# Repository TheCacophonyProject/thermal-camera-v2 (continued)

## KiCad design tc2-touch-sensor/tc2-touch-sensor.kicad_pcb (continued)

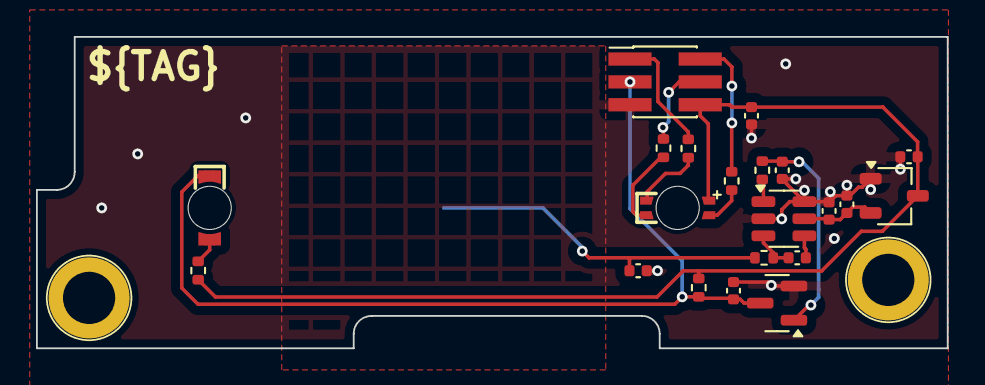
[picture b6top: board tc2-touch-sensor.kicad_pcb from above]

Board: 6 copper layers, 50.6 x 17.3 mm, 24 parts (1 on the bottom side), 16 nets.

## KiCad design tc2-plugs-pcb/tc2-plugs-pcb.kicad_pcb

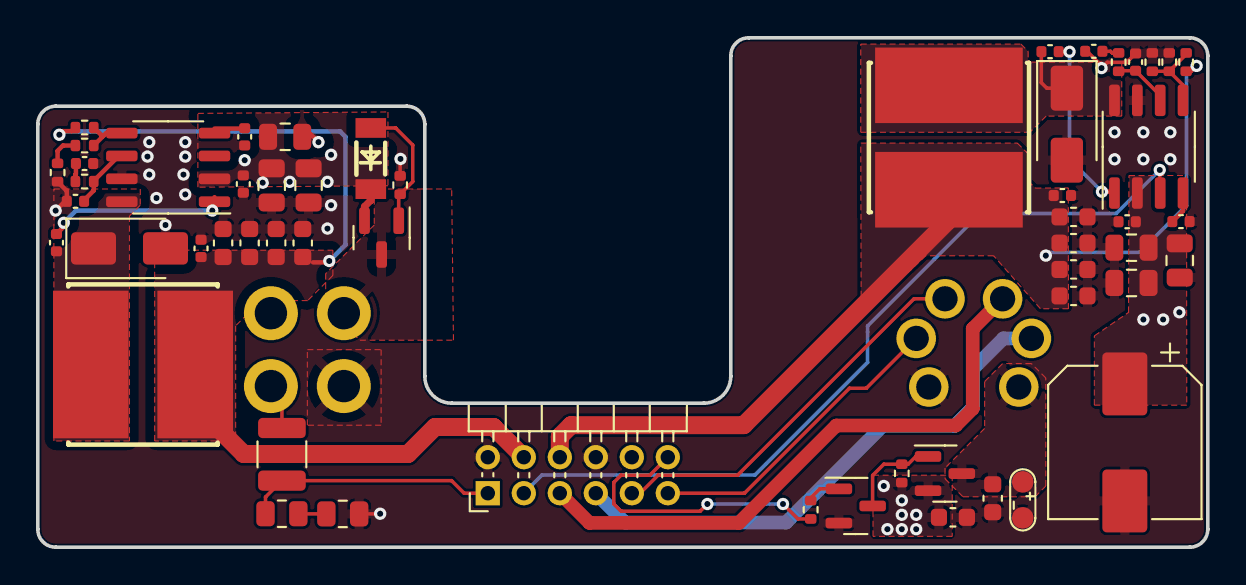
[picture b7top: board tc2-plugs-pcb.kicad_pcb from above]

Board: 4 copper layers, 65.0 x 28.3 mm, 57 parts (0 on the bottom side), 31 nets.

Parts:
C101, C102, C103, C104, C106, C107: 22uF; C_0805_2012Metric
C105: 220uF; CP_Elec_8x10
C108, C129: 10uF; C_0603_1608Metric
C109, C110, C111, C112, C119, C120: 1nF; C_0402_1005Metric
C113, C114: 47pF; C_0402_1005Metric
C115, C116: 10nF; C_0402_1005Metric
C117, C118: 100nF; C_0402_1005Metric
C121, C122, C123, C124, C125, C126, C127, C128: 22uF; C_0603_1608Metric
D101: D_Zener; LL-34_L3.5-W1.5-RD
D102, D103: D_Shockley; D_SMA
J102: JCON_M16_04Pin; jcon-4pin_m16
J103: JCON_M16_06Pin; jcon-6pin-m16
J104: Conn_02x06_Odd_Even; PinHeader_2x06_P2.00mm_Horizontal
L101, L102: 6.8uF; IND-SMD_L8.0-W8.0_1217AS
Q101, Q102: Q_PMOS_GSD; SOT-23
Q103: 2N7002; SOT-23
R101: 2M; R_1210_3225Metric
R102: 150k; R_0805_2012Metric
R103: 22k; R_0805_2012Metric
R104, R110, R112, R113: 100k; R_0402_1005Metric
R105, R106: 33k; R_0402_1005Metric
R107: 150k; R_0402_1005Metric
R108, R111: 22k; R_0402_1005Metric
R109: 10k; R_0402_1005Metric
R114: 1k; R_0402_1005Metric
TP101: TestPoint_2Pole; test-point-2p
U101, U102: TPS54331; SO-8_3.9x4.9mm_P1.27mm

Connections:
5V_EN: J104.3, U101.3 (EN)
+3V3: C120.1, C122.1, C124.1, C126.1, C128.1, J104.4, L102.2, R112.1
+5V: C119.1, C121.1, C123.1, C125.1, C127.1, J104.6, L101.2, R110.1
+12V: C101.1, C102.1, C103.1, C104.1, C105.1, C106.1, C107.1, C109.1, C110.1, C129.1, D101.1 (K), Q101.2 (S), Q102.2 (S), R113.2, U101.2 (VIN), U102.2 (VIN)
/+Batt: J102.4, R101.1
/SW_3V3: C118.2, D103.1 (K), L102.1, U102.8 (PH)
/SW_5V: C117.2, D102.1 (K), L101.1, U101.8 (PH)
BATT_SENSE: J104.1, R101.2, R102.1
EN_PERIPH: J104.12, R114.1
GND: C101.2, C102.2, C103.2, C104.2, C105.2, C106.2, C107.2, C108.2, C109.2, C110.2, C111.2, C112.2, C113.2, C114.2, C115.2, C116.2, C119.2, C120.2, C121.2, C122.2, C123.2, C124.2, C125.2, C126.2, C127.2, C128.2, C129.2, D102.2 (A), D103.2 (A), J102.1, J103.1, J104.2, J104.8, Q103.2 (S), R103.2, R104.2, R107.1, R109.2, R111.1, TP101.1, U101.7 (GND), U102.7 (GND)
unnamed: C111.1, R105.2
unnamed: C112.1, R106.2
unnamed: D101.2 (A), Q101.1 (G), R104.1
unnamed: Q102.1 (G), Q103.3 (D), R113.1
unnamed: Q103.1 (G), R114.2
unnamed: R102.2, R103.1
unnamed: R108.1, R109.1
unnamed: C117.1, U101.1 (BOOT)
unnamed: C113.1, R105.1, U101.6 (COMP)
unnamed: C115.1, U101.4 (SS)
unnamed: R107.2, R110.2, R111.2, U101.5 (VSENSE)
unnamed: C118.1, U102.1 (BOOT)
unnamed: C114.1, R106.1, U102.6 (COMP)
unnamed: C116.1, U102.4 (SS)
unnamed: R108.2, R112.2, U102.5 (VSENSE)
OUT_RX: J103.2, J104.11
OUT_TX: J103.3, J104.9
SPEAKER_+: J103.4, J104.5
SPEAKER_-: J103.5, J104.7
VIN: J102.2, Q101.3 (D)
VOUT: C108.1, J103.6, Q102.3 (D), TP101.2

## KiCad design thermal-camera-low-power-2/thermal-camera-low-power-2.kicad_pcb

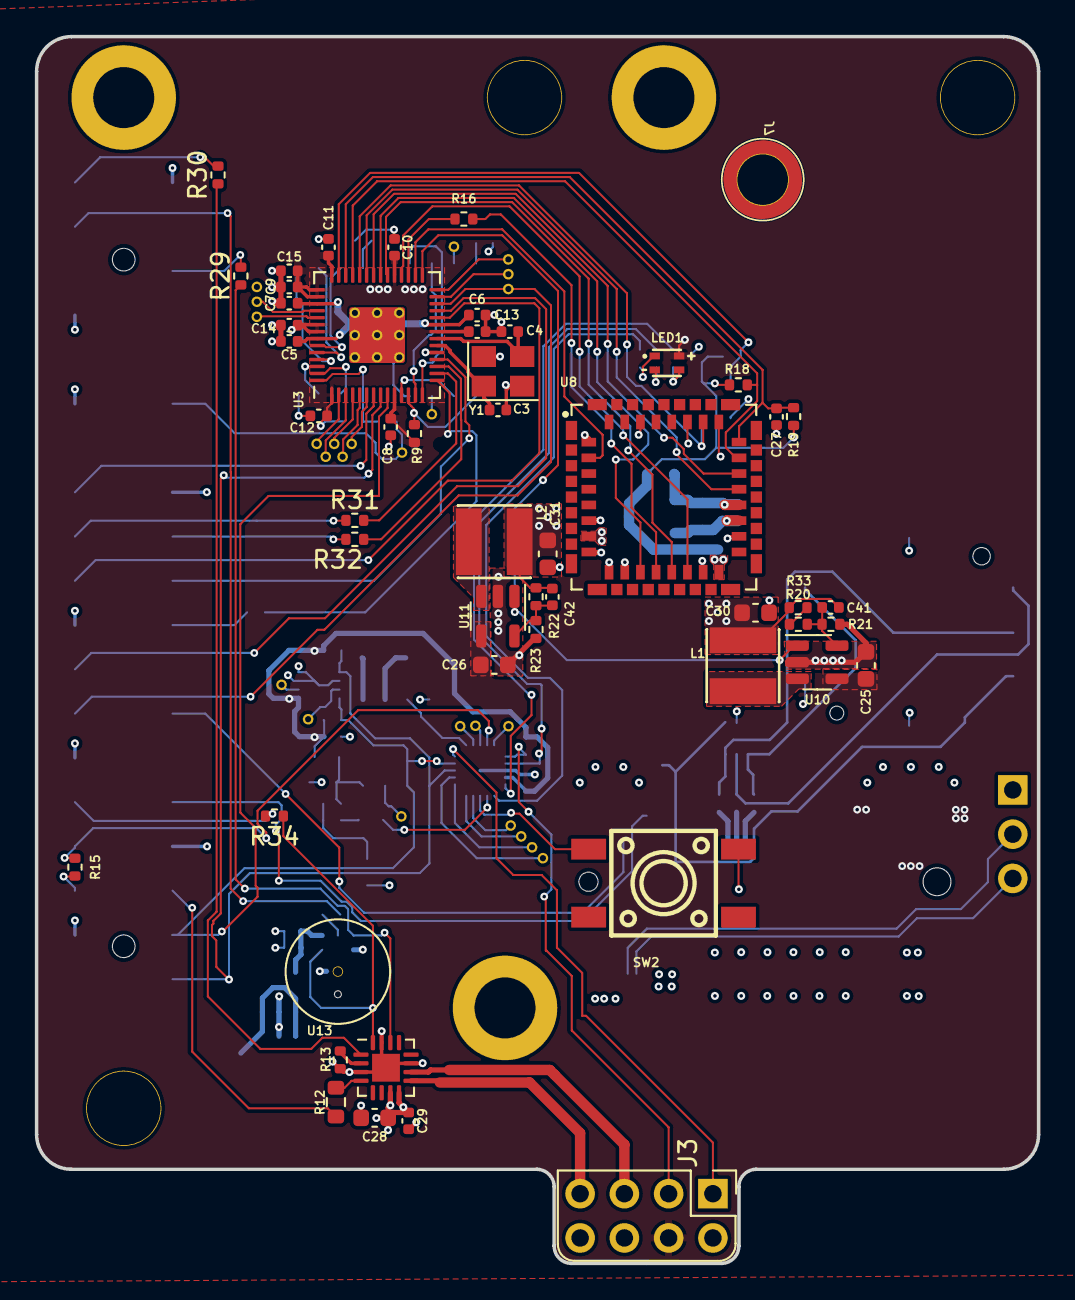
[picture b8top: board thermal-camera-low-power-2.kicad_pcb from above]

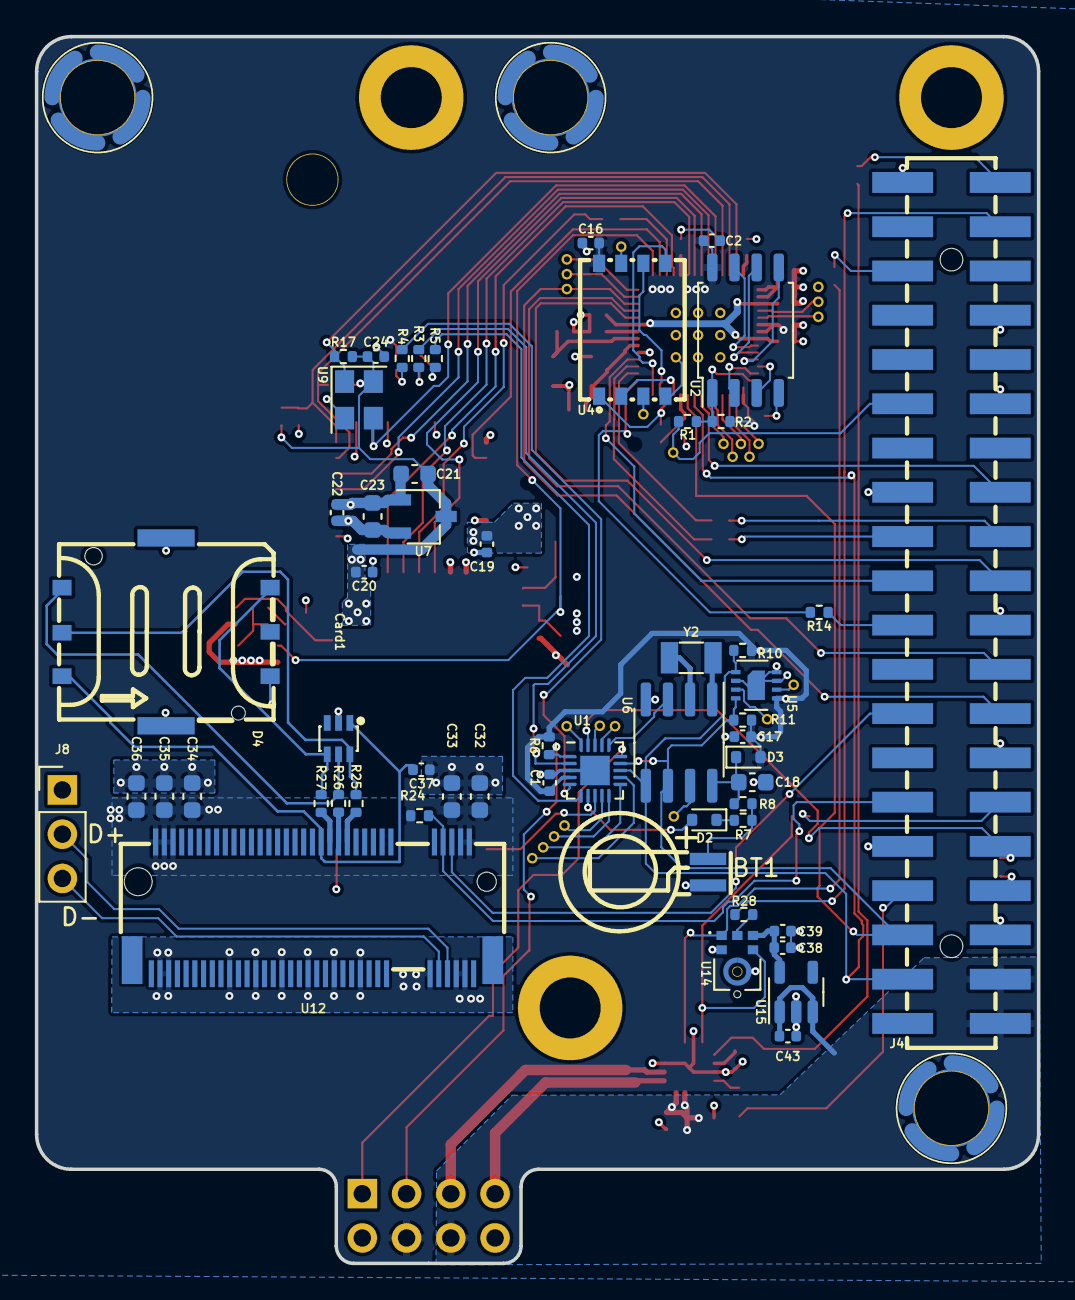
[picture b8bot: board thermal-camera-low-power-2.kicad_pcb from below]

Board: 4 copper layers, 57.5 x 70.4 mm, 136 parts (69 on the bottom side), 115 nets.

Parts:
BT1: Battery_Cell; CAP-SMD_FL11E
C1, C2, C5, C6, C8, C10, C11, C12, C13, C14, C15, C16, C17, C19, C20, C22, C24, C27, C29, C37, C38: 220nF; C_0402_1005Metric
C3, C4, C39, C41, C42: 12pF; C_0402_1005Metric
C7, C9: 1u; C_0402_1005Metric
C18, C21, C23, C25, C26, C28, C30, C31, C32, C33, C34, C35, C36: 10uF; C_0603_1608Metric
C43: 1uF; C_0402_1005Metric
Card1: SIM-Nano; SIM-SMD_SMN-304
D2, D3: D; D_SOD-523
D4: SMF05CT1G; SOT-363_L2.0-W1.3-P0.65-LS2.1-BR
H1, H2, H3: MountingHole; Mouning_Hole_M3
J1, J5, J6: Screw_Terminal_01x01; SMTSO25
J3: Conn_02x04_Odd_Even; power-pcb
J4: Raspberry_Pi_2_3; RPI_HDR-SMD_40P-P2.54-V-F-R2-C20-S8.7-EH
J7: Screw_Terminal_01x01; SMD_BD4.4-L4.4-D2.8
J8: Conn_01x03; PinHeader_1x03_P2.54mm_Vertical
L1, L2: 4.7uH; IND-SMD_L4.0-W4.0_SWPA4018S
LED1: NH-B1515RGBA-HF; LED-ARRAY-SMD_4P-L1.6-W1.5-TL_NH-B1515RGBA
R1, R7, R8, R15: 1k; R_0402_1005Metric
R2: DNF; R_0402_1005Metric
R3, R4, R5: 180R; R_0402_1005Metric
R6, R9, R13, R17, R18, R19, R21, R22, R23, R24: 100k; R_0402_1005Metric
R10, R11, R33: 10k; R_0402_1005Metric
R12: 1M; R_0603_1608Metric
R14, R16, R25, R26, R27, R28, R29, R30, R31, R32, R34: 22ohm; R_0402_1005Metric
R20: 390k; R_0402_1005Metric
SW2: K2-6639SP-M4SC-04; KEY-SMD_4P-L6.0-W6.0-P3.90-LS9.0
TP1, TP2, TP3, TP4, TP5, TP6, TP7, TP8, TP9, TP10, TP11, TP12, TP13, TP14, TP15, TP16, TP17, TP26, TP27, TP40, TP41, TP44, TP46, TP47: TestPoint; TP
U1: ATtiny1616-M; VQFN-20-1EP_3x3mm_P0.4mm_EP1.7x1.7mm
U2: W25Q128JVS; SOIC-8_5.23x5.23mm_P1.27mm
U3: RP2040; RP2040-QFN-56
U4: MT29F2G01ABAGDWB-IT; U-PDFN-8_L6.0-W8.0-P1.27-BL
U5: SHT30-DIS; Sensirion_DFN-8-1EP_2.5x2.5mm_P0.5mm_EP1.1x1.7mm
U6: PCF8563T; SOIC-8_3.9x4.9mm_P1.27mm
U7: ME6216A28XG; TSOT-23
U8: Flir_LEPTON; MOLEX_105028-1001
U9: 3N25000G33YC; Oscillator_SMD_Abracon_ASE-4Pin_3.2x2.5mm
U10, U11: TD6810; TSOT-23-5
U12: SIM7600G-H-M.2; M.2
U13: MAX98357; TQFN-16-1EP_3x3mm_P0.5mm_EP1.6x1.6mm
U14: SPH0645LM4H; MIC_SPH0645LM4H-B
U15: ME6211; SOT-23-5
Y1: Crystal_GND24; Crystal_SMD_3225-4Pin_3.2x2.5mm
Y2: Crystal; Crystal_SMD_3215-2Pin_3.2x1.5mm

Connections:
4G_POWER_ON: J4.15 (GPIO22), U12.6 (~FUL_CARD_POWER_OFF)
4G_USB_D+: J8.2, U12.7 (USB_D+)
4G_USB_D-: J8.3, U12.9 (USB_D-)
5V_EN: J3.3, R6.1, U1.1 (PA2)
+1V1: C5.1, C6.1, C7.1, U3.23 (DVDD), U3.45 (VREG_VOUT), U3.50 (DVDD)
+1V2: C19.1, C31.1, C42.2, L2.2, R22.2, U8.7 (VDDC)
+2V8: C22.1, C23.1, U7.2 (VO), U8.19 (VDD)
+3V0: C20.1, C21.1, C24.1, C30.1, C41.2, L1.2, R17.2, R18.1, R19.1, R33.2, U7.3 (VI), U8.16 (VDDIO), U9.4 (VDD)
+3V3: C1.2, C2.1, C8.1, C9.1, C10.1, C11.1, C12.1, C13.1, C14.1, C15.1, C16.1, C17.2, C25.1, C26.1, C32.1, C33.1, C34.1, C35.1, C36.1, D3.2 (A), J3.4, LED1.2 (+), R2.1, R6.2, R9.2, R10.1, R11.1, R24.1, U1.4 (VCC), U2.8 (VCC), U3.1 (IOVDD), U3.10 (IOVDD), U3.22 (IOVDD), U3.33 (IOVDD), U3.42 (IOVDD), U3.43 (ADC_AVDD), U3.44 (VREG_IN), U3.48 (USB_VDD), U3.49 (IOVDD), U4.8 (VCC), U5.5 (VDD), U10.4 (VDD), U11.4 (VDD), U12.2 (VBAT), U12.4 (VBAT), U12.70 (VBAT), U12.72 (VBAT), U12.74 (VBAT)
+3V3_Lin: C38.2, C39.2, U14.5 (VDD), U15.5 (Vout)
+5V: C28.1, C29.1, C43.2, J3.6, J4.2 (5V), J4.4 (5V), U13.7 (VDD), U13.8 (VDD), U15.1 (Vin), U15.3 (CE)
/Lepton/FB_1V2: C42.1, R22.1, R23.1, U11.5 (FB)
/Lepton/FB_3V0: C41.1, R20.1, R21.1, U10.5 (FB)
/Lepton/SW_1V2: L2.1, U11.3 (SW)
/Lepton/SW_3V0: L1.1, U10.3 (SW)
/USB_D+: TP47.1, U3.47 (USB_DP)
/USB_D-: TP46.1, U3.46 (USB_DM)
ATtiny_RESET_UPDI: J4.10 (GPIO15/RXD), R15.1, U1.19 (~RESET/PA0)
BATT_SENSE: J3.1, U1.15 (PC0)
BOOT_MODE: J4.29 (GCLK1/GPIO5), R1.2, TP44.1
GND: BT1.2 (-), C1.1, C2.2, C3.1, C4.1, C5.2, C6.2, C7.2, C8.2, C9.2, C10.2, C11.2, C12.2, C13.2, C14.2, C15.2, C16.2, C17.1, C18.2, C19.2, C20.2, C21.2, C22.2, C23.2, C24.2, C25.2, C26.2, C27.2, C28.2, C29.2, C30.2, C31.2, C32.2, C33.2, C34.2, C35.2, C36.2, C37.1, C38.1, C39.1, C43.1, Card1.1 (GND), Card1.2 (GND), Card1.C5 (GND), D4.2, J3.2, J3.8, J4.6 (GND), J4.9 (GND), J4.14 (GND), J4.20 (GND), J4.25 (GND), J4.30 (GND), J4.34 (GND), J4.39 (GND), J8.1, R13.2, R21.2, R23.2, SW2.2, TP9.1, U1.3 (GND), U1.21 (GND), U2.4 (GND), U3.19 (TESTEN), U3.57 (GND), U4.4 (VSS), U5.2 (ADDR), U5.7 (R), U5.8 (VSS), U5.9 (VSS), U6.4 (VSS), U7.1 (GND), U8.1 (GND), U8.6 (GND), U8.8 (GND), U8.9 (GND), U8.10 (GND), U8.15 (GND), U8.18 (GND), U8.20 (GND), U8.25 (GND), U8.27 (GND), U8.30 (GND), U9.2 (GND), U10.2 (GND), U11.2 (GND), U12.3 (GND), U12.5 (GND), U12.11 (GND), U12.27 (GND), U12.33 (GND), U12.39 (GND), U12.45 (GND), U12.51 (GND), U12.57 (GND), U12.71 (GND), U12.73 (GND), U13.3 (GND), U13.11 (GND), U13.15 (GND), U13.17 (GND), U14.2 (SEL), U14.3 (GND), U15.2 (Vss), Y1.2, Y1.4
I2S_BCLK: R34.1, U13.16 (BCLK), U14.4 (BCLK)
I2S_DIN: J4.38 (GPIO20/MOSI1), R28.2
I2S_DOUT: R30.1, U13.1 (DIN)
I2S_LRCLK: R29.1, U13.14 (LRCLK), U14.1 (WS)
LED_B: LED1.3 (-), R4.2
LED_G: LED1.4 (-), R3.2
LED_R: LED1.1 (-), R5.2
LEPTON_CLK_EN: R17.1, U3.41 (GPIO29_ADC3), U9.1 (EN)
LEPTON_I2C_SCL: U3.37 (GPIO25), U8.21 (SCL)
LEPTON_I2C_SDA: U3.36 (GPIO24), U8.22 (SDA)
LEPTON_MASTER_CLK: U3.38 (GPIO26_ADC0), U8.26 (MASTER_CLK), U9.3 (OUT)
LEPTON_POWER_EN: U3.29 (GPIO18), U10.1 (Run), U11.1 (Run)
LEPTON_PWR_DWN_L: R18.2, U3.39 (GPIO27_ADC1), U8.23 (PWR_DWN_L)
LEPTON_RESET_L: C27.1, R19.2, U3.40 (GPIO28_ADC2), U8.24 (RESET_L)
LEPTON_SPI_CS: U3.32 (GPIO21), U8.14 (SPI_CS_L)
LEPTON_SPI_MISO: R16.1, U3.31 (GPIO20)
LEPTON_SPI_MOSI: U3.35 (GPIO23), U8.11 (SPI_MOSI)
LEPTON_SPI_SCLK: U3.34 (GPIO22), U8.13 (SPI_CLK)
LEPTON_VSYNC: U3.30 (GPIO19), U8.2 (GPIO3)
MEM_SPI_MISO: U3.11 (GPIO8), U4.2 (SO/IO1)
MEM_SPI_MOSI: U3.14 (GPIO11), U4.5 (SI/IO0)
MEM_SPI_SCLK: U3.13 (GPIO10), U4.6 (SCK)
MEM_SPI_~CS: R9.1, U3.12 (GPIO9), U4.1 (~CS)
unnamed: BT1.1 (+), R7.1, R8.2
unnamed: Card1.C3 (CLK), D4.5, R26.2
unnamed: Card1.C7 (I/O), D4.4, R27.2
unnamed: Card1.C2 (RST), D4.6, R25.2
unnamed: C37.2, Card1.C1 (VCC), D4.1, U12.36 (USIM_VDD)
unnamed: D2.1 (K), R7.2
unnamed: C18.1, D3.1 (K), R8.1, U6.8 (VDD)
unnamed: J4.8 (GPIO14/TXD), R15.2
unnamed: J4.12 (GPIO18/PWM0), R34.2
unnamed: J4.35 (GPIO19/MISO1), R29.2
unnamed: J4.40 (GPIO21/SCLK1), R30.2
unnamed: J4.19 (MOSI0/GPIO10), R14.1
unnamed: J4.23 (SCLK0/GPIO11), R32.1
unnamed: J4.24 (~CE0/GPIO8), R31.1
unnamed: R20.2, R33.1
unnamed: TP3.1, U1.20 (PA1)
unnamed: R3.1, U1.2 (PA3)
unnamed: R4.1, U1.5 (PA4)
unnamed: R5.1, U1.6 (PA5)
unnamed: SW2.1, U1.8 (PA7)
unnamed: TP4.1, U1.12 (PB2)
unnamed: TP5.1, U1.11 (PB3)
unnamed: TP6.1, U1.10 (PB4)
unnamed: TP7.1, U1.9 (PB5)
unnamed: TP1.1, U1.17 (PC2)
unnamed: TP2.1, U1.18 (PC3)
unnamed: TP10.1, U3.2 (GPIO0)
unnamed: TP11.1, U3.3 (GPIO1)
unnamed: TP12.1, U3.4 (GPIO2)
unnamed: TP13.1, U3.5 (GPIO3)
unnamed: TP14.1, U3.6 (GPIO4)
unnamed: TP26.1, U3.27 (GPIO16)
unnamed: TP27.1, U3.28 (GPIO17)
unnamed: C3.2, U3.20 (XIN), Y1.1
unnamed: C4.2, U3.21 (XOUT), Y1.3
unnamed: TP41.1, U4.7 (~HOLD/IO3)
unnamed: TP40.1, U4.3 (~WP/IO2)
unnamed: TP15.1, U5.3 (ALERT)
unnamed: TP16.1, U5.6 (~RESET)
unnamed: TP17.1, U6.7 (CLKO)
unnamed: U6.1 (OSCI), Y2.2
unnamed: U6.2 (OSCO), Y2.1
unnamed: R16.2, U8.12 (SPI_MISO)
unnamed: R26.1, U12.32 (USIM_CLK)
unnamed: R27.1, U12.34 (USIM_DATA)
unnamed: R25.1, U12.30 (USIM_RST)
unnamed: R13.1, U13.2 (GAIN_SLOT)
unnamed: R12.2, U13.4 (~SD_MODE)
unnamed: R28.1, U14.6 (DATA)
QSPI_SCLK: U2.6 (CLK), U3.52 (QSPI_SCLK)
QSPI_SD0: U2.5 (DI(IO0)), U3.53 (QSPI_SD0)
QSPI_SD1: U2.2 (DO(IO1)), U3.55 (QSPI_SD1)
QSPI_SD2: U2.3 (IO2), U3.54 (QSPI_SD2)
QSPI_SD3: U2.7 (IO3), U3.51 (QSPI_SD3)
QSPI_SS: R1.1, R2.2, U2.1 (~CS), U3.56 (QSPI_SS)
RPI_PING: J4.26 (~CE1/GPIO7), U3.7 (GPIO5)
RPI_SPI_CS: R31.2, U3.16 (GPIO13)
RPI_SPI_MISO: J4.21 (MISO0/GPIO9), U3.18 (GPIO15)
RPI_SPI_MOSI: R14.2, U3.15 (GPIO12)
RPI_SPI_SCLK: R32.2, U3.17 (GPIO14)
RTC_BT_SENSE: D2.2 (A), U1.7 (PA6)
RUN: J4.16 (GPIO23), TP8.1, U3.26 (RUN)
SCL: J4.5 (SCL/GPIO3), R11.2, U1.14 (PB0), U3.9 (GPIO7), U5.4 (SCL), U6.6 (SCL)
SDA: J4.3 (SDA/GPIO2), R10.2, U1.13 (PB1), U3.8 (GPIO6), U5.1 (SDA), U6.5 (SDA)
SPEAKER_+: J3.7, U13.9 (UOTP)
SPEAKER_-: J3.5, U13.10 (OUTN)
SPEAKER_SD_MODE: J4.7 (GCLK0/GPIO4), R12.1
SWD: J4.18 (GPIO24), U3.25 (SWD)
SW_CLK: J4.22 (GPIO25), U3.24 (SWCLK)
~RTC_INT: U1.16 (PC1), U6.3 (~INT)
~W_DISABLE1: J4.11 (GPIO17), R24.2, U12.8 (~W_DISABLE1)

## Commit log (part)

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2022-11-13 WIP 2
2023-04-17 Low power WIP
2023-05-10 Low power version WIP
2023-05-25 file tidy up
2023-05-30 Clean up of files and updated drawings for PCBs
2023-06-15 Version 2 WIP
2023-06-27 Thermal camera V2 WIP
2023-09-04 P2 milestone
2023-11-23 P3-Nov release
2023-11-23 Update boarder for power PCB
2024-03-23 v0.4.0
2024-05-04 Small update for v0.4.1
2024-05-30 panelize WIP
2024-06-12 Adding panel
2024-06-13 v0.5.3
2024-06-13 Update gitignore
2024-08-19 Update to use touch sensor
2024-09-06 Small updates
2024-09-07 Change to through hole connector and add simcard PCB to pannel
2024-09-28 Version v0.7.0
2024-10-25 version v0.7.1
2024-11-05 v0.7.2 panelise microphone boards
2024-11-08 Made microphone PCB wider to make it easier for v cutting
2024-11-08 Remove old panel file
2024-12-02 v0.7.3
2025-01-24 New power changes WIP
2025-01-24 Add .tar.gz to gitignore
2025-02-09 Fixed panel tabs
2025-03-05 0.8.0 WIP
2025-03-06 Updated to use field LCSC Part instead of LCSC for the JLCPCB part number
2025-03-06 Tidy up of files
2025-03-07 Tidy up
2025-03-12 Update to kicad 9, fix microphone panel v cuts
2025-04-27 Upgraded to new kicad version
2025-04-27 Tidy up for making an order for v0.7.3
2026-02-23 Add license file
